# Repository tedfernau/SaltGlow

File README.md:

# SaltGlow

A portable saltlamp for camping, reading, or just setting the mood. 

Simple materials for modern living: Salt, Copper, Wood. 

Features: \
-USBC rechargable in less than 2 hours (100 minutes) (dumb charger only)\
-11 hour battery life - Max Brightness\
-about 5.5 days battery life - Low Brightness\
-3 Brightness Settings\
-Simple Materials\
-Each Lamp is Unique\
-Hand Assembled and Salt Selected\
-Designed in USA\
-Small Batch\

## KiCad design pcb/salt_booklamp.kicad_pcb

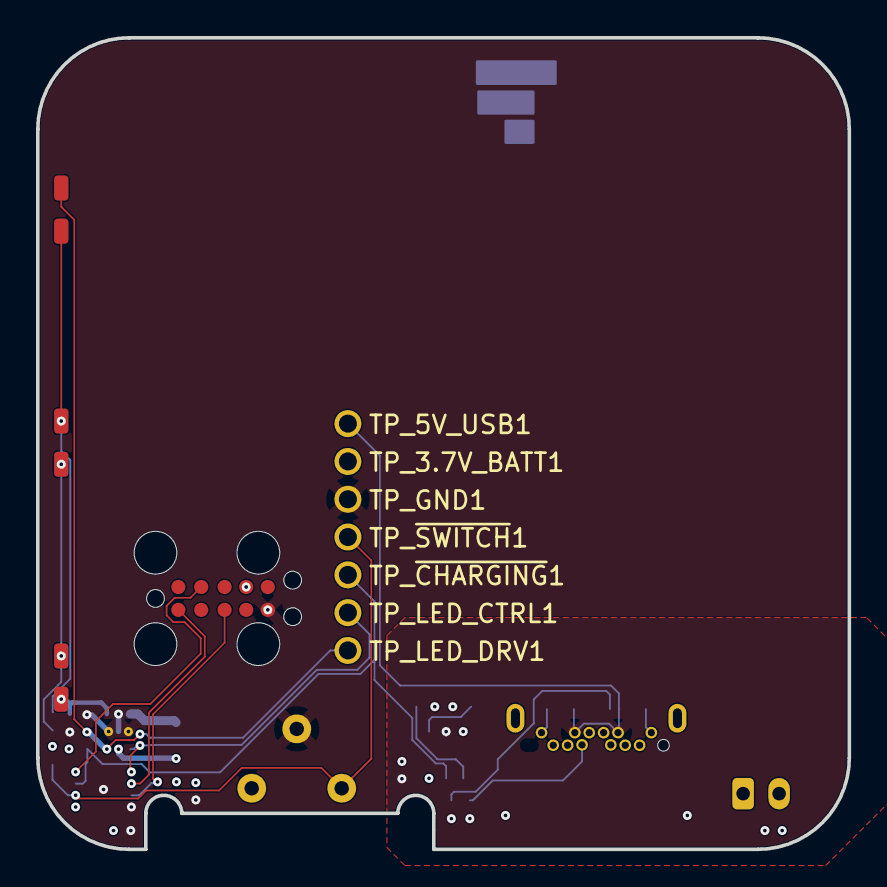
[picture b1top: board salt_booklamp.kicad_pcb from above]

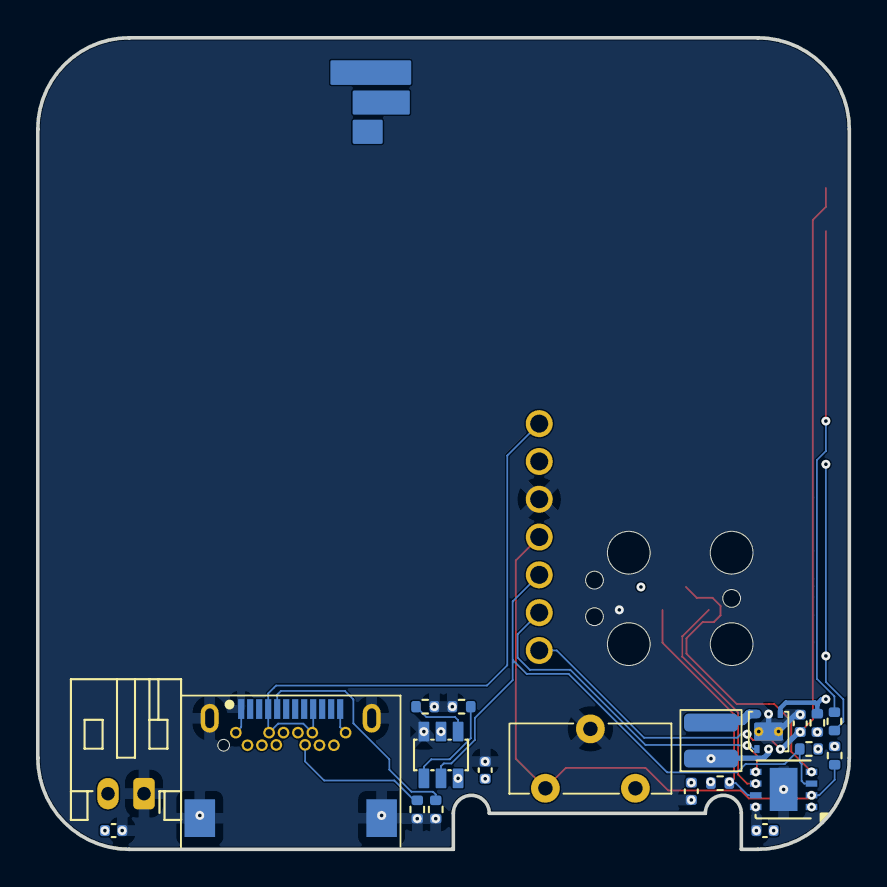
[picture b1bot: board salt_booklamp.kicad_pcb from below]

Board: 4 copper layers, 45.1 x 45.1 mm, 32 parts (21 on the bottom side), 18 nets.

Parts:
BATT1: S2B-PH-K-S; JST_PH_S2B-PH-K_1x02_P2.00mm_Horizontal
C1, C2, C3, C4, C5: 1uF; C_0402_1005Metric
J1: USB-C31-S-RA-CS1E-BK-T/R; USB-C31-S-RA-CS1E-BK
L1: 22uH; ind_VLS3012CX
LED1, LED2, LED3: SMS1105UWDW; LED_SMS1105UWDW
P1: PIC-TC2050-IDC; TC2050-IDC
R1, R3, R4, R5: 10k0; R_0402_1005Metric
R2: 6r8; R_0402_1005Metric
R6: 1k2; R_0402_1005Metric
R8: 0r0; R_0402_1005Metric
R9, R10: 5k1; R_0402_1005Metric
S1: CL-SB-12C-12; CL-SB-12C-11
TP_3.7V_BATT1, TP_5V_USB1: 1-pin header
TP_GND1: 1-pin header
TP_LED_CTRL1: 1-pin header
TP_LED_DRV1: 1-pin header
TP_~{CHARGING}1: 1-pin header
TP_~{SWITCH}1: 1-pin header
U1: PIC16F15213T-I/MF; DFN-8-1EP_3x3mm_P0.65mm_EP1.55x2.4mm
U2: BQ21040DBVR
U3: TPS61158DRVR; 6-WDFN - TPS61158DRVR

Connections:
+3.7_VBATT: BATT1.2 (+), C2.1, C3.1, C5.1, L1.1, P1.7 (VDD), R3.2, R4.2, R5.2, TP_3.7V_BATT1.1, U1.1 (VDD), U2.2 (VOUT), U3.2 (VIN)
+5V_USB: C1.1, J1.A4 (VBUS), J1.A9 (VBUS), J1.B4 (VBUS), J1.B9 (VBUS), TP_5V_USB1.1, U2.6 (VIN)
/LED_CTRL: TP_LED_CTRL1.1, U1.5 (RA2), U3.1 (CTRL)
/LED_DRV: C4.1, LED1.A (a), TP_LED_DRV1.1, U3.3 (VOUT)
/LED_DRV_SW: L1.2, U3.6 (LX)
/~CHARGING: R4.1, TP_~{CHARGING}1.1, U1.3 (RA4), U2.3 (~CHG)
/~SWITCH: R3.1, S1.1, TP_~{SWITCH}1.1, U1.2 (RA5)
GND: BATT1.1 (-), C1.2, C2.2, C3.2, C4.2, C5.2, J1.0 (mount), J1.A1 (GND), J1.A12 (GND), J1.B1 (GND), J1.B12 (GND), P1.5 (GND), R1.1, R2.1, R6.2, R9.2, R10.2, S1.2, TP_GND1.1, U1.8 (VSS), U2.5 (GND), U3.5 (GND), U3.7 (Thermal)
unnamed: J1.A5 (CC1), R9.1
unnamed: J1.B5 (CC2), R10.1
unnamed: LED1.K (k), LED3.A (a), R8.2
unnamed: LED2.A (a), LED3.K (k), R8.1
unnamed: LED2.K (k), R2.2, U3.4 (FB)
unnamed: P1.1 (ICSPCLK), U1.6 (RA1/ICSPCLK)
unnamed: P1.3 (ICSPDAT), R5.1, U1.7 (RA0/ICSPDAT)
unnamed: P1.9 (~MCLR), U1.4 (RA3/MCLR/VPP)
unnamed: R6.1, U2.4 (ISET)
unnamed: R1.2, U2.1 (TS)

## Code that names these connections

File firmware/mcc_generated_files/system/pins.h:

/**
 * Generated Pins header File
 * 
 * @file pins.h
 * 
 * @defgroup  pinsdriver Pins Driver
 * 
 * @brief This is generated driver header for pins. 
 *        This header file provides APIs for all pins selected in the GUI.
 *
 * @version Driver Version  3.0.0
*/

/*
© [2026] Microchip Technology Inc. and its subsidiaries.

    Subject to your compliance with these terms, you may use Microchip 
    software and any derivatives exclusively with Microchip products. 
    You are responsible for complying with 3rd party license terms  
    applicable to your use of 3rd party software (including open source  
    software) that may accompany Microchip software. SOFTWARE IS ?AS IS.? 
    NO WARRANTIES, WHETHER EXPRESS, IMPLIED OR STATUTORY, APPLY TO THIS 
    SOFTWARE, INCLUDING ANY IMPLIED WARRANTIES OF NON-INFRINGEMENT,  
    MERCHANTABILITY, OR FITNESS FOR A PARTICULAR PURPOSE. IN NO EVENT 
    WILL MICROCHIP BE LIABLE FOR ANY INDIRECT, SPECIAL, PUNITIVE, 
    INCIDENTAL OR CONSEQUENTIAL LOSS, DAMAGE, COST OR EXPENSE OF ANY 
    KIND WHATSOEVER RELATED TO THE SOFTWARE, HOWEVER CAUSED, EVEN IF 
    MICROCHIP HAS BEEN ADVISED OF THE POSSIBILITY OR THE DAMAGES ARE 
    FORESEEABLE. TO THE FULLEST EXTENT ALLOWED BY LAW, MICROCHIP?S 
    TOTAL LIABILITY ON ALL CLAIMS RELATED TO THE SOFTWARE WILL NOT 
    EXCEED AMOUNT OF FEES, IF ANY, YOU PAID DIRECTLY TO MICROCHIP FOR 
    THIS SOFTWARE.
*/

#ifndef PINS_H
#define PINS_H

#include <xc.h>

#define INPUT   1
#define OUTPUT  0

#define HIGH    1
#define LOW     0

#define ANALOG      1
#define DIGITAL     0

#define PULL_UP_ENABLED      1
#define PULL_UP_DISABLED     0

// get/set IO_RA2 aliases
#define LED_CTRL_TRIS                 TRISAbits.TRISA2
#define LED_CTRL_LAT                  LATAbits.LATA2
#define LED_CTRL_PORT                 PORTAbits.RA2
#define LED_CTRL_WPU                  WPUAbits.WPUA2
#define LED_CTRL_OD                   ODCONAbits.ODCA2
#define LED_CTRL_ANS                  ANSELAbits.ANSA2
#define LED_CTRL_SetHigh()            do { LATAbits.LATA2 = 1; } while(0)
#define LED_CTRL_SetLow()             do { LATAbits.LATA2 = 0; } while(0)
#define LED_CTRL_Toggle()             do { LATAbits.LATA2 = ~LATAbits.LATA2; } while(0)
#define LED_CTRL_GetValue()           PORTAbits.RA2
#define LED_CTRL_SetDigitalInput()    do { TRISAbits.TRISA2 = 1; } while(0)
#define LED_CTRL_SetDigitalOutput()   do { TRISAbits.TRISA2 = 0; } while(0)
#define LED_CTRL_SetPullup()          do { WPUAbits.WPUA2 = 1; } while(0)
#define LED_CTRL_ResetPullup()        do { WPUAbits.WPUA2 = 0; } while(0)
#define LED_CTRL_SetPushPull()        do { ODCONAbits.ODCA2 = 0; } while(0)
#define LED_CTRL_SetOpenDrain()       do { ODCONAbits.ODCA2 = 1; } while(0)
#define LED_CTRL_SetAnalogMode()      do { ANSELAbits.ANSA2 = 1; } while(0)
#define LED_CTRL_SetDigitalMode()     do { ANSELAbits.ANSA2 = 0; } while(0)
// get/set IO_RA4 aliases
#define CHARGING_N_TRIS                 TRISAbits.TRISA4
#define CHARGING_N_LAT                  LATAbits.LATA4
#define CHARGING_N_PORT                 PORTAbits.RA4
#define CHARGING_N_WPU                  WPUAbits.WPUA4
#define CHARGING_N_OD                   ODCONAbits.ODCA4
#define CHARGING_N_ANS                  ANSELAbits.ANSA4
#define CHARGING_N_SetHigh()            do { LATAbits.LATA4 = 1; } while(0)
#define CHARGING_N_SetLow()             do { LATAbits.LATA4 = 0; } while(0)
#define CHARGING_N_Toggle()             do { LATAbits.LATA4 = ~LATAbits.LATA4; } while(0)
#define CHARGING_N_GetValue()           PORTAbits.RA4
#define CHARGING_N_SetDigitalInput()    do { TRISAbits.TRISA4 = 1; } while(0)
#define CHARGING_N_SetDigitalOutput()   do { TRISAbits.TRISA4 = 0; } while(0)
#define CHARGING_N_SetPullup()          do { WPUAbits.WPUA4 = 1; } while(0)
#define CHARGING_N_ResetPullup()        do { WPUAbits.WPUA4 = 0; } while(0)
#define CHARGING_N_SetPushPull()        do { ODCONAbits.ODCA4 = 0; } while(0)
#define CHARGING_N_SetOpenDrain()       do { ODCONAbits.ODCA4 = 1; } while(0)
#define CHARGING_N_SetAnalogMode()      do { ANSELAbits.ANSA4 = 1; } while(0)
#define CHARGING_N_SetDigitalMode()     do { ANSELAbits.ANSA4 = 0; } while(0)
#define RA4_SetInterruptHandler  CHARGING_N_SetInterruptHandler
// get/set IO_RA5 aliases
#define SWITCH_N_TRIS                 TRISAbits.TRISA5
#define SWITCH_N_LAT                  LATAbits.LATA5
#define SWITCH_N_PORT                 PORTAbits.RA5
#define SWITCH_N_WPU                  WPUAbits.WPUA5
#define SWITCH_N_OD                   ODCONAbits.ODCA5
#define SWITCH_N_ANS                  ANSELAbits.ANSA5
#define SWITCH_N_SetHigh()            do { LATAbits.LATA5 = 1; } while(0)
#define SWITCH_N_SetLow()             do { LATAbits.LATA5 = 0; } while(0)
#define SWITCH_N_Toggle()             do { LATAbits.LATA5 = ~LATAbits.LATA5; } while(0)
#define SWITCH_N_GetValue()           PORTAbits.RA5
#define SWITCH_N_SetDigitalInput()    do { TRISAbits.TRISA5 = 1; } while(0)
#define SWITCH_N_SetDigitalOutput()   do { TRISAbits.TRISA5 = 0; } while(0)
#define SWITCH_N_SetPullup()          do { WPUAbits.WPUA5 = 1; } while(0)
#define SWITCH_N_ResetPullup()        do { WPUAbits.WPUA5 = 0; } while(0)
#define SWITCH_N_SetPushPull()        do { ODCONAbits.ODCA5 = 0; } while(0)
#define SWITCH_N_SetOpenDrain()       do { ODCONAbits.ODCA5 = 1; } while(0)
#define SWITCH_N_SetAnalogMode()      do { ANSELAbits.ANSA5 = 1; } while(0)
#define SWITCH_N_SetDigitalMode()     do { ANSELAbits.ANSA5 = 0; } while(0)
#define RA5_SetInterruptHandler  SWITCH_N_SetInterruptHandler
/**
 * @ingroup  pinsdriver
 * @brief GPIO and peripheral I/O initialization
 * @param none
 * @return none
 */
void PIN_MANAGER_Initialize (void);

/**
 * @ingroup  pinsdriver
 * @brief Interrupt on Change Handling routine
 * @param none
 * @return none
 */
void PIN_MANAGER_IOC(void);

/**
 * @ingroup  pinsdriver
 * @brief Interrupt on Change Handler for the CHARGING_N pin functionality
 * @param none
 * @return none
 */
void CHARGING_N_ISR(void);

/**
 * @ingroup  pinsdriver
 * @brief Interrupt Handler Setter for CHARGING_N pin interrupt-on-change functionality.
 *        Allows selecting an interrupt handler for CHARGING_N at application runtime.
 * @pre Pins intializer called
 * @param InterruptHandler function pointer.
 * @return none
 */
void CHARGING_N_SetInterruptHandler(void (* InterruptHandler)(void));

/**
 * @ingroup  pinsdriver
 * @brief Dynamic Interrupt Handler for CHARGING_N pin.
 *        This is a dynamic interrupt handler to be used together with the CHARGING_N_SetInterruptHandler() method.
 *        This handler is called every time the CHARGING_N ISR is executed and allows any function to be registered at runtime.
 * @pre Pins intializer called
 * @param none
 * @return none
 */
extern void (*CHARGING_N_InterruptHandler)(void);

/**
 * @ingroup  pinsdriver
 * @brief Default Interrupt Handler for CHARGING_N pin. 
 *        This is a predefined interrupt handler to be used together with the CHARGING_N_SetInterruptHandler() method.
 *        This handler is called every time the CHARGING_N ISR is executed. 
 * @pre Pins intializer called
 * @param none
 * @return none
 */
void CHARGING_N_DefaultInterruptHandler(void);

/**
 * @ingroup  pinsdriver
 * @brief Interrupt on Change Handler for the SWITCH_N pin functionality
 * @param none
 * @return none
 */
void SWITCH_N_ISR(void);

/**
 * @ingroup  pinsdriver
 * @brief Interrupt Handler Setter for SWITCH_N pin interrupt-on-change functionality.
 *        Allows selecting an interrupt handler for SWITCH_N at application runtime.
 * @pre Pins intializer called
 * @param InterruptHandler function pointer.
 * @return none
 */
void SWITCH_N_SetInterruptHandler(void (* InterruptHandler)(void));

/**
 * @ingroup  pinsdriver
 * @brief Dynamic Interrupt Handler for SWITCH_N pin.
 *        This is a dynamic interrupt handler to be used together with the SWITCH_N_SetInterruptHandler() method.
 *        This handler is called every time the SWITCH_N ISR is executed and allows any function to be registered at runtime.
 * @pre Pins intializer called
 * @param none
 * @return none
 */
extern void (*SWITCH_N_InterruptHandler)(void);

/**
 * @ingroup  pinsdriver
 * @brief Default Interrupt Handler for SWITCH_N pin. 
 *        This is a predefined interrupt handler to be used together with the SWITCH_N_SetInterruptHandler() method.
 *        This handler is called every time the SWITCH_N ISR is executed. 
 * @pre Pins intializer called
 * @param none
 * @return none
 */
void SWITCH_N_DefaultInterruptHandler(void);


#endif // PINS_H
/**
 End of File
*/

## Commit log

2025-04-04 Add mechanical files
2025-04-04 uploading project files
2025-06-10 start creating an assembly
2025-06-23 prepare for Rev 0.2 schematic changes
2025-06-25 Add CC resistors to schematic for USB compliant smart chargers
2025-06-26 Changed 0603 parts to 0402, assigned 0402 uF cap MPN, still need to assign 0402 Resistor MPNs
2025-07-02 Changed MCU to smaller DFN package, add Connector footprint to PCB (very big), add shield pins to USB footprint to remove warning
2025-07-03 Moved battery voltage measurement to a different programming pin
2025-07-07 Start placement - new LED placement
2025-07-08 Placement work
2025-07-16 changed placement of a couple resistors to achieve daily commit
2025-07-17 Start updating light guide plate
2025-07-18 Work on placement for pcb .step transfer
2025-07-22 light guide plate work
2025-07-25 remove old light guide plate sketches, rename light guide plate sketches
2025-07-25 make light guide plate 6.0 sketch
2025-07-28 placement work - may need smaller battery connector
2025-07-29 initial placement for mechanical design -> redesign light guide for 3 LEDs, improve enclosure fit of PCB etc., evaluate battery connector
2025-07-29 redesign light guide for 3 LEDs
2025-07-30 Redo LGP model and cleanup
2025-08-12 adjust net classes and start routing
2025-08-13 add test point and clean up schematic
2025-08-14 made a CAM project to explore manufacturing process
2025-08-15 adjust placement of edge components in PCA, added lanyard hole in wood enclosure, updated light guide .dxf file, updated mirror film .dxf file, exported wood enclosure .step for quote, exported light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
2025-08-16 Change size of internal routing on switch cover, add more meat to switch cover/switch interface, start work adjusting retainer plate
2025-08-26 Routing work
2025-09-10 ordered pca, wood, copper, batteries
2025-09-10 ordered lgp, switch retainer plate
2025-09-26 exported mirror film outline, blackout film outline, and diffuser film outline for ordering
2025-11-24 build7 fixes - interposer for pcb error, new switch retainer, new mirror film, adhesive film to test
2026-02-03 Current status: need to assemble and test interposers then build some test units. Checking in any changes while this has been dormant.
2026-04-21 Current status: debugged and fixed 4 boards, need to finalize firmware and finish building these 4. All lamps from first build came unglued, need to revise design/assembly to fix this
2026-05-02 finished simple firmware for testing, going to build up these 4 for testing
